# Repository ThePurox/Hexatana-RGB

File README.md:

# Hexatana
Hexatana is a 36 katana-inspired keyboard designed around [hexagonal keycaps](https://hw.s-ol.nu/HEX-keycaps/).

# Soldering
## MCU
The first step is to solder the RP2040 to the top center of the PCB.
You can use pin headers to align the MCU on the solder pads.
The orientation if the MCU should be such that the USB-C port is on the top side of the main PCB.
The bottom side of the main PCB has six katanas printed in its center.
So to solder the MCU in place, put the main PCB on your soldering surface, such that you do not see the six katanas, place the MCU onto of the PCB such that the USB-port is facing you.
You can now optionally stabilize the MCU with pin headers and solder the MCU to the main PCB.

## Soldering in the diodes
There exist two versions of the PCB, one has silkscreen marking for the orientation of the diodes, in the other one the shape of the solderpads indicates the direction of the diodes.

### silkscreen marking
On the top side of the PCB you will find a lot of `U`-shaped markings in with `Dx` where `x` is a number $\in \{1-36,73\}$ next to them
The top side of the diodes shows a vertical line followed by the letters T4, i.e. it looks like  `|T4`.
The diode has to be solder to the PCB such that the vertical line is on the closed side of the `U`-marking.
A soldered diode should look like the one in the following picture.

Solder in all 37 diodes that way.
Diodes `D1-D36` are in the center of the PCB, diode `D73` is $\approx 4\,\mathrm{cm}$ right of the MCU.

### Solderpad marking
To clean up the PCB the silkscreen markings for the diodes were removed.
The diodes shall be soldered in to the footprints were one pad is rectangular, and the other pad is pentagonal.
The pointy bit of the pentagon points to the kathode. I.e. the line marking on the diode need to be soldered to the rectangular pad.
The right direction is shown in the following picture.

Solder in all 37 diodes.
36 Diodes are in the center of the PCB, the final diode is $\approx 4\,\mathrm{cm}$ right of the MCU.

## Testing the keyboard
Now the keyboard should be functional.
You can test that by plugging the keyboard into a computer and opening a text editor of your choice.
Turn the keyboard around, such that you can see the 6 katanas and grab yourself a pair of metal tweezers or a pair of scissors.
Connect two adjacent solder pads.
A key press corresponding to the following keymap should be registered
<!-- Now a letter should appear on your keyboard. -->
<!-- Repeat these steps for all solderpads connected with white paint. -->
<!-- In your text editor you should see the letters `a-z` and the numbers `0-9`. -->
<!-- The default keymap of the keyboard is -->
```
  q w e r t      z u i o p
 a s d f g        h j k l OSS
y x c v b          n m , . -
    CTRL ESC    TAB ALT
        SPACE  ENTER
```
, where `OSS` is one-shot-shift.
Note the keymap presented here is show with the keyboard in its natural orientation.
You are probably holding it the other way round so you should a mirrored keymap.
If one of them didn't show up, this likely means that one of the diodes is not soldered in correctly.
When all keys work we can install the hot-swap sockets which will allow us to mount the switches.
However before we do those it is advisable to first install the optional LED-backlight.

## Backlight (optional)
### Soldering in the LEDs
It is now time to solder in the LEDs.
The PCB should be orientated such that you can see the 6 swords.
There are 36 small rectangular cutouts in the PCB (labeled `D37-D72`) in which the LEDs will be placed.
#### Orientation of the LEDs
The LEDs emit light only on one side (the one with the transparent cover).
This side needs to be placed face down, i.e. facing the table.
Now we still have one rotational degree of freedom, which we will eliminate in the following.
Just as the diodes, the light emitting diodes (LEDs) are sensitive to the orientation in which they are soldered in.
One of the metal legs of the LEDs is cut at an angle.
This leg has to be placed at the white `L`-shaped marking next to the hole for the LED.
This fixes the last rotational degree of freedom of each LED, and you can solder in the LEDs.
Be very careful with the orientation of the LEDs!
Their orientation changes when going from one row to the next row and going from the left side of the keyboard to the right side of the keyboard.
Only the thumb clusters are consistent in the orientation of the LEDs.
The LEDs are also very sensitive to temperature, so be careful when soldering them to the PCB.

### Picking a position for the solder jumper / picking a voltage for the first LED
Turn the keyboard around once more, such that you can no longer see the swords and the MCU is facing away from you.
#### Background
Approximately $3\,\mathrm{cm}$ to the right side of the MCU you will find a solder-jumper.
It is used to pick between two possible voltages powering the first LED of the backlight.
The datalines of the backlight-LEDs are not specified to work with the 3.3V supplied by the MCU, when the LEDs are driven by (the standard) 5V.
However usually they do still work in that scenario.
The PCB implements a hack [hack](https://hackaday.com/2017/01/20/cheating-at-5v-ws2812-control-to-use-a-3-3v-data-line/) for the unlucky chance that the LEDs do not work when the data line is driven by 3.3V and the LEDs are driven by 5V.
The hack exploits the fact, that when the first LED is powered by 4.3V, 3.3V are in spec for the dataline.
The solder jumper let's you pick whether the first LED is powered by 5V or 4.3V.
I suggest you try 5V first as all LEDs will have the same brightness that way.
Powering the first LED with a lower voltage might lead to a slightly dimmer first LED.

The center pad of the jumper is connected to the power line of the LED.
The bottom pad is connected to 5V.
The top pad has a voltage of 4.3V.
The diode just above the jumper reduces the 5V to 4.3V.

#### What to do
Bridge the center and bottom pads of the jumper, and connect the keyboard to a computer.
If all LEDs light up you can go ahead to soldering in the [hotswap sockets](#installing-the-hot-swap-sockets)
If some of the LEDs light up double check the solder joints of the LED with the highest number that is lighting up and the one with the smallest number that is not lighting up. There is most likely a problem there.
An Led might also be fried by excessive heat during soldering.
If the plastic of the LED has melted, the LED is probably dead; replace it with a new one. There a four more LEDs in the kit than you need.
If no LED lights up you might be one of the (un)lucky people with an LED produced to specification. There are two options on how to proceed.
1) you can try replacing the first LED (`D37`) and see whether the LEDs light up now, or
2) remove the solder from the solder jumper on the top side of the PCB and bridge the center pad with the top pad. Now the LED is powered with 4.3V and the 3.3V on the dataline are in spec.

### Installing stabilising capacitors (very optional)
There are 6 spots for capacitors next to the outer most switches of the top three key-rows.
The capacitors can be soldered onto the PCB to stabilise the power of the LEDs, however everything should work without them.

## Installing the hot-swap sockets
Turn the keyboard around, such that you can see the 6 swords again.
Now solder the hot-swap sockets onto the last solderpads that are not connected to anything yet.

## Installing the switches
Now turn the keyboard around one last time and install the switches and keycaps.

# Flashing Firmware
## QMK
The ncecessary files for a [QMK-firmware](https://qmk.fm) can be found in the [firmware directory](./qmk-firmware).
## VIAL
[Exen904](https://github.com/exen904) was so kind and build a [VIAL](https://get.vial.today/) firmware which can be found [here](https://github.com/exen904/vial-qmk/tree/exen904/keyboards/purox/hexatana)
## ZMK
There is a basic [zmk](https://github.com/ThePurox/hexatana-zmk/) repository.
Feel free to fork it and adjust everything to your liking.

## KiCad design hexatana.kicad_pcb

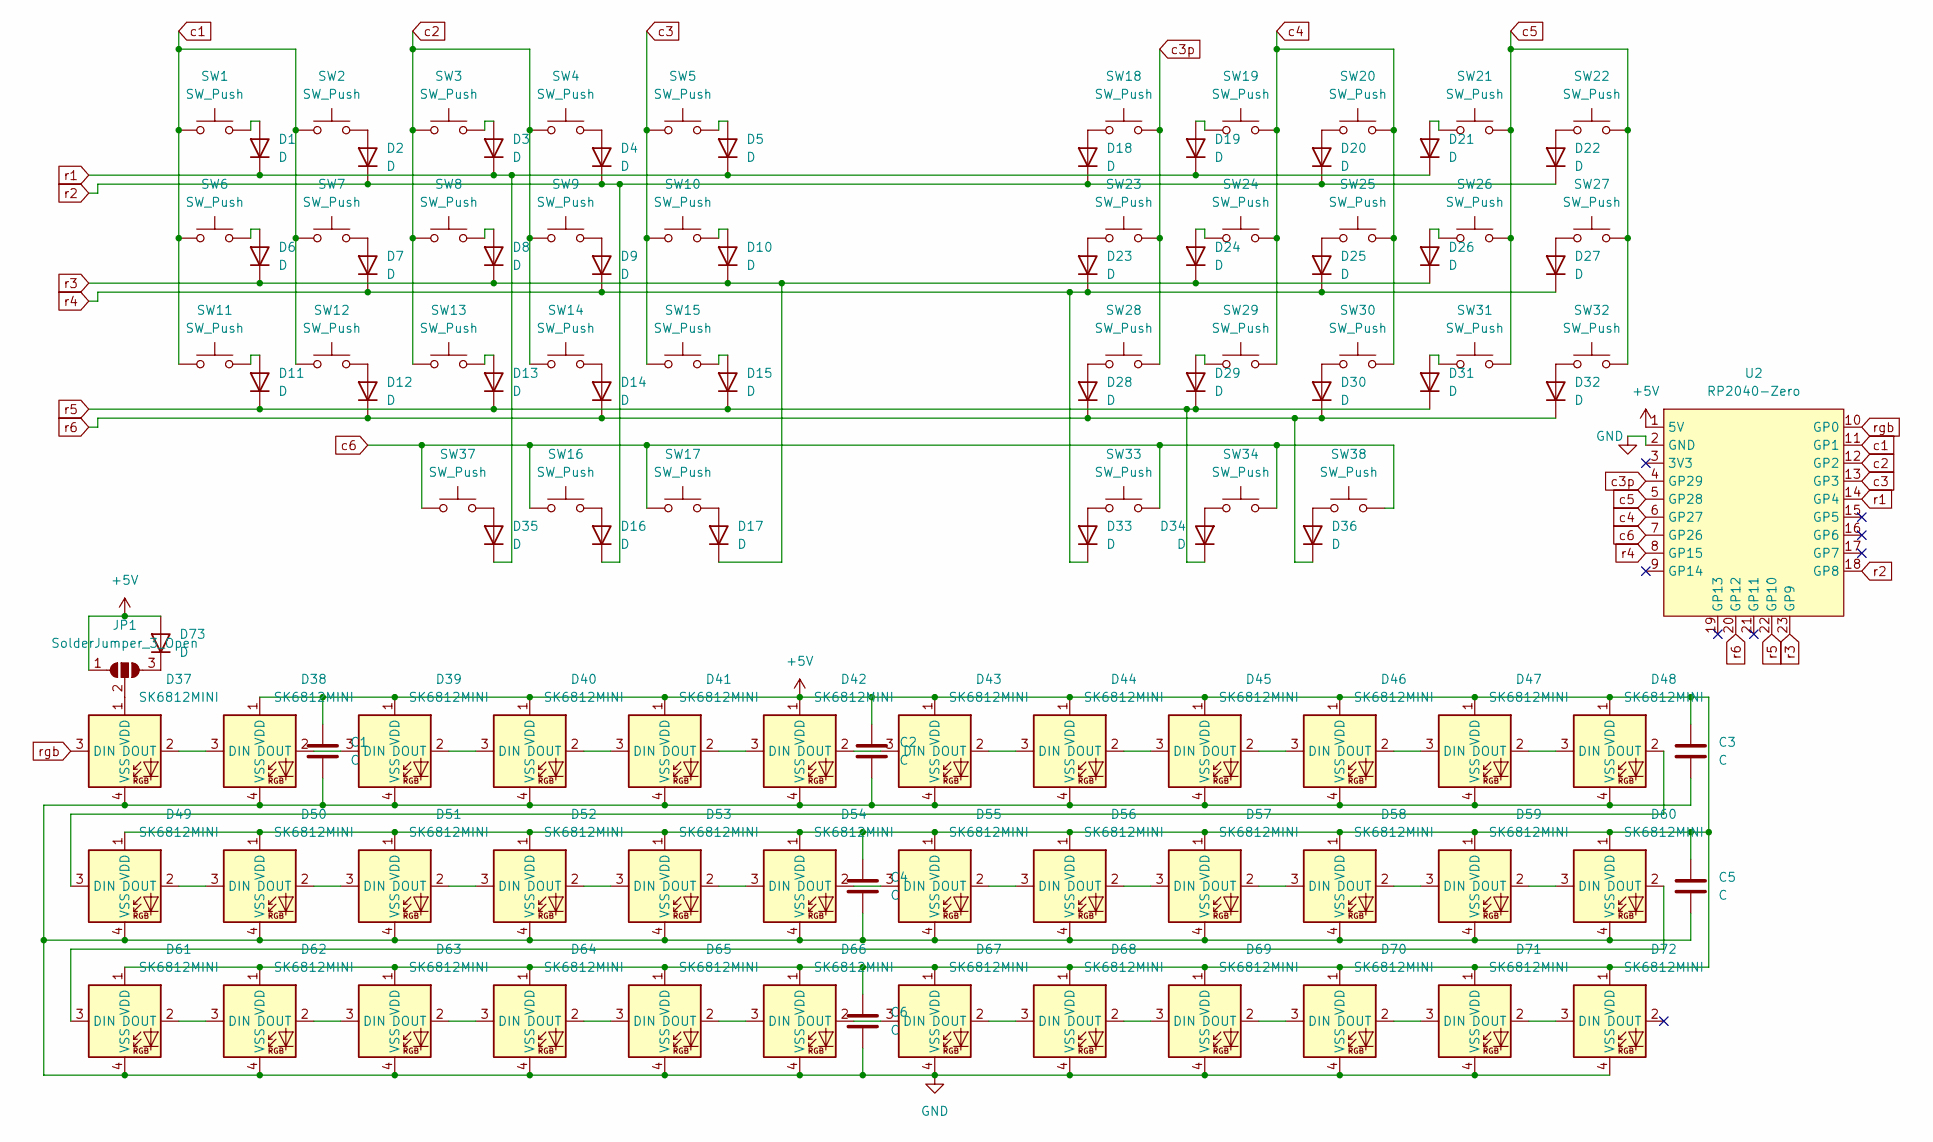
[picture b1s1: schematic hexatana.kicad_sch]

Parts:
C1, C2, C3, C4, C5, C6: C; C_0603_1608Metric_Pad1.08x0.95mm_HandSolder
D1, D2, D3, D4, D5, D6, D7, D8, D9, D10, D11, D12, D13, D14, D15, D16, D17, D18, D19, D20, D21, D22, D23, D24, D25, D26, D27, D28, D29, D30, D31, D32, D33, D34, D35, D36, D73: D; D_SOD-123
D37, D38, D39, D40, D41, D42, D43, D44, D45, D46, D47, D48, D49, D50, D51, D52, D53, D54, D55, D56, D57, D58, D59, D60, D61, D62, D63, D64, D65, D66, D67, D68, D69, D70, D71, D72: SK6812MINI; LED_6028R
JP1: SolderJumper_3_Open; SolderJumper-3_P1.3mm_Open_RoundedPad1.0x1.5mm
SW1, SW2, SW3, SW4, SW5, SW6, SW7, SW8, SW9, SW10, SW11, SW12, SW13, SW14, SW15, SW16, SW17, SW18, SW19, SW20, SW21, SW22, SW23, SW24, SW25, SW26, SW27, SW28, SW29, SW30, SW31, SW32, SW33, SW34, SW37, SW38: SW_Push; PG1350_hotswap
U2: RP2040-Zero; RP2040 Zero

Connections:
+5V: C1.1, C2.1, C3.1, C4.1, C5.1, C6.1, D38.1 (VDD), D39.1 (VDD), D40.1 (VDD), D41.1 (VDD), D42.1 (VDD), D43.1 (VDD), D44.1 (VDD), D45.1 (VDD), D46.1 (VDD), D47.1 (VDD), D48.1 (VDD), D49.1 (VDD), D50.1 (VDD), D51.1 (VDD), D52.1 (VDD), D53.1 (VDD), D54.1 (VDD), D55.1 (VDD), D56.1 (VDD), D57.1 (VDD), D58.1 (VDD), D59.1 (VDD), D60.1 (VDD), D61.1 (VDD), D62.1 (VDD), D63.1 (VDD), D64.1 (VDD), D65.1 (VDD), D66.1 (VDD), D67.1 (VDD), D68.1 (VDD), D69.1 (VDD), D70.1 (VDD), D71.1 (VDD), D72.1 (VDD), D73.2 (A), JP1.1 (A), U2.1 (5V)
GND: C1.2, C2.2, C3.2, C4.2, C5.2, C6.2, D37.4 (VSS), D38.4 (VSS), D39.4 (VSS), D40.4 (VSS), D41.4 (VSS), D42.4 (VSS), D43.4 (VSS), D44.4 (VSS), D45.4 (VSS), D46.4 (VSS), D47.4 (VSS), D48.4 (VSS), D49.4 (VSS), D50.4 (VSS), D51.4 (VSS), D52.4 (VSS), D53.4 (VSS), D54.4 (VSS), D55.4 (VSS), D56.4 (VSS), D57.4 (VSS), D58.4 (VSS), D59.4 (VSS), D60.4 (VSS), D61.4 (VSS), D62.4 (VSS), D63.4 (VSS), D64.4 (VSS), D65.4 (VSS), D66.4 (VSS), D67.4 (VSS), D68.4 (VSS), D69.4 (VSS), D70.4 (VSS), D71.4 (VSS), D72.4 (VSS), U2.2 (GND)
unnamed: D1.2 (A), SW1.2
unnamed: D2.2 (A), SW2.2
unnamed: D3.2 (A), SW3.2
unnamed: D4.2 (A), SW4.2
unnamed: D5.2 (A), SW5.2
unnamed: D6.2 (A), SW6.2
unnamed: D7.2 (A), SW7.2
unnamed: D8.2 (A), SW8.2
unnamed: D9.2 (A), SW9.2
unnamed: D10.2 (A), SW10.2
unnamed: D11.2 (A), SW11.2
unnamed: D12.2 (A), SW12.2
unnamed: D13.2 (A), SW13.2
unnamed: D14.2 (A), SW14.2
unnamed: D15.2 (A), SW15.2
unnamed: D16.2 (A), SW16.2
unnamed: D17.2 (A), SW17.2
unnamed: D18.2 (A), SW18.1
unnamed: D19.2 (A), SW19.1
unnamed: D20.2 (A), SW20.1
unnamed: D21.2 (A), SW21.1
unnamed: D22.2 (A), SW22.1
unnamed: D23.2 (A), SW23.1
unnamed: D24.2 (A), SW24.1
unnamed: D25.2 (A), SW25.1
unnamed: D26.2 (A), SW26.1
unnamed: D27.2 (A), SW27.1
unnamed: D28.2 (A), SW28.1
unnamed: D29.2 (A), SW29.1
unnamed: D30.2 (A), SW30.1
unnamed: D31.2 (A), SW31.1
unnamed: D32.2 (A), SW32.1
unnamed: D33.2 (A), SW33.1
unnamed: D34.2 (A), SW34.1
unnamed: D35.2 (A), SW37.2
unnamed: D36.2 (A), SW38.1
unnamed: D37.2 (DOUT), D38.3 (DIN)
unnamed: D37.1 (VDD), JP1.2 (C)
unnamed: D38.2 (DOUT), D39.3 (DIN)
unnamed: D39.2 (DOUT), D40.3 (DIN)
unnamed: D40.2 (DOUT), D41.3 (DIN)
unnamed: D41.2 (DOUT), D42.3 (DIN)
unnamed: D42.2 (DOUT), D43.3 (DIN)
unnamed: D43.2 (DOUT), D44.3 (DIN)
unnamed: D44.2 (DOUT), D45.3 (DIN)
unnamed: D45.2 (DOUT), D46.3 (DIN)
unnamed: D46.2 (DOUT), D47.3 (DIN)
unnamed: D47.2 (DOUT), D48.3 (DIN)
unnamed: D48.2 (DOUT), D49.3 (DIN)
unnamed: D49.2 (DOUT), D50.3 (DIN)
unnamed: D50.2 (DOUT), D51.3 (DIN)
unnamed: D51.2 (DOUT), D52.3 (DIN)
unnamed: D52.2 (DOUT), D53.3 (DIN)
unnamed: D53.2 (DOUT), D54.3 (DIN)
unnamed: D54.2 (DOUT), D55.3 (DIN)
unnamed: D55.2 (DOUT), D56.3 (DIN)
unnamed: D56.2 (DOUT), D57.3 (DIN)
unnamed: D57.2 (DOUT), D58.3 (DIN)
unnamed: D58.2 (DOUT), D59.3 (DIN)
unnamed: D59.2 (DOUT), D60.3 (DIN)
unnamed: D60.2 (DOUT), D61.3 (DIN)
unnamed: D61.2 (DOUT), D62.3 (DIN)
unnamed: D62.2 (DOUT), D63.3 (DIN)
unnamed: D63.2 (DOUT), D64.3 (DIN)
unnamed: D64.2 (DOUT), D65.3 (DIN)
unnamed: D65.2 (DOUT), D66.3 (DIN)
unnamed: D66.2 (DOUT), D67.3 (DIN)
unnamed: D67.2 (DOUT), D68.3 (DIN)
unnamed: D68.2 (DOUT), D69.3 (DIN)
unnamed: D69.2 (DOUT), D70.3 (DIN)
unnamed: D70.2 (DOUT), D71.3 (DIN)
unnamed: D71.2 (DOUT), D72.3 (DIN)
unnamed: D73.1 (K), JP1.3 (B)
c1: SW1.1, SW2.1, SW6.1, SW7.1, SW11.1, SW12.1, U2.11 (GP1)
c2: SW3.1, SW4.1, SW8.1, SW9.1, SW13.1, SW14.1, U2.12 (GP2)
c3: SW5.1, SW10.1, SW15.1, U2.13 (GP3)
c3p: SW18.2, SW23.2, SW28.2, U2.4 (GP29)
c4: SW19.2, SW20.2, SW24.2, SW25.2, SW29.2, SW30.2, U2.6 (GP27)
c5: SW21.2, SW22.2, SW26.2, SW27.2, SW31.2, SW32.2, U2.5 (GP28)
c6: SW16.1, SW17.1, SW33.2, SW34.2, SW37.1, SW38.2, U2.7 (GP26)
r1: D1.1 (K), D3.1 (K), D5.1 (K), D19.1 (K), D21.1 (K), D35.1 (K), U2.14 (GP4)
r2: D2.1 (K), D4.1 (K), D16.1 (K), D18.1 (K), D20.1 (K), D22.1 (K), U2.18 (GP8)
r3: D6.1 (K), D8.1 (K), D10.1 (K), D17.1 (K), D24.1 (K), D26.1 (K), U2.23 (GP9)
r4: D7.1 (K), D9.1 (K), D23.1 (K), D25.1 (K), D27.1 (K), D33.1 (K), U2.8 (GP15)
r5: D11.1 (K), D13.1 (K), D15.1 (K), D29.1 (K), D31.1 (K), D34.1 (K), U2.22 (GP10)
r6: D12.1 (K), D14.1 (K), D28.1 (K), D30.1 (K), D32.1 (K), D36.1 (K), U2.20 (GP12)
rgb: D37.3 (DIN), U2.10 (GP0)

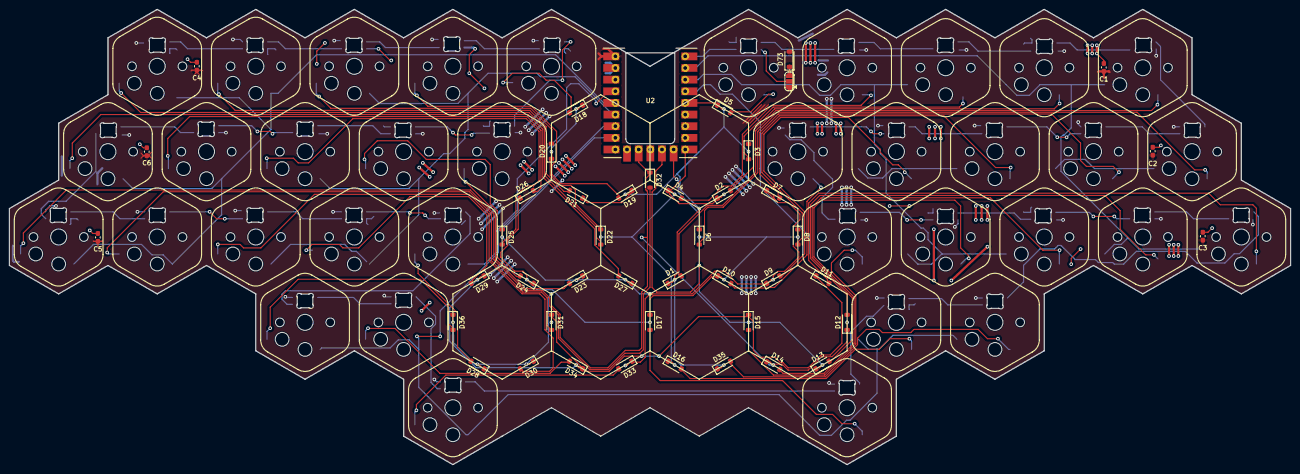
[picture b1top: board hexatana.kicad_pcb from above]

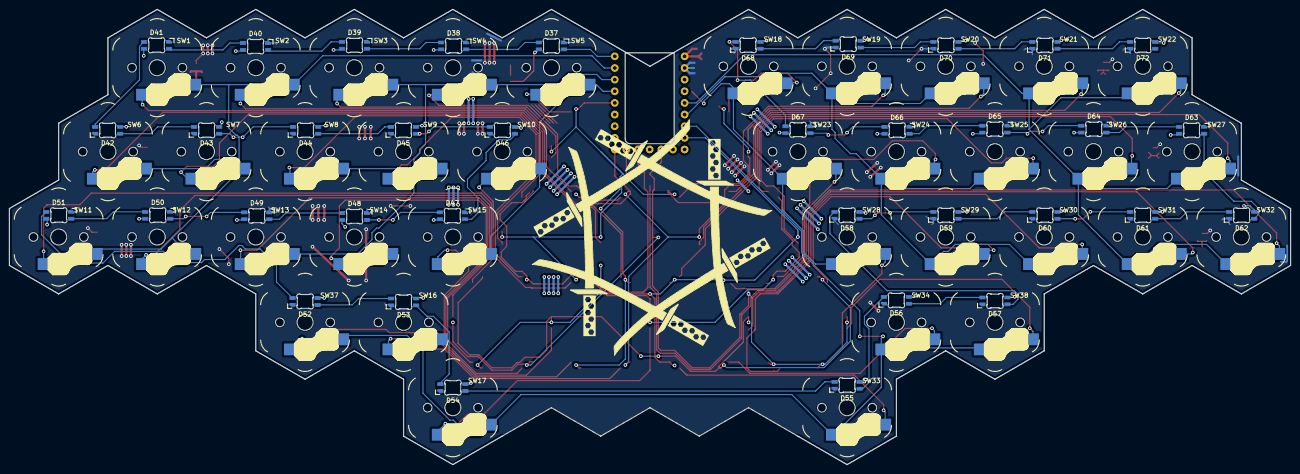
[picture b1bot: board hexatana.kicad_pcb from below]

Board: 2 copper layers, 279.5 x 99.3 mm, 117 parts (72 on the bottom side), 89 nets.

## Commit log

2024-01-08 simple version with ugly routing
2024-01-29 before hexed-ground
2024-02-17 final tm
2024-03-07 added Buildguide and qmk-firmware files
2024-03-07 added pictures
2024-03-07 proper pictures, fixed keymap
2024-03-07 fixed curly braces
2024-03-07 units
2024-03-07 fixed qmk link
2024-03-07 removed second readme
2024-03-07 added capacitors
2024-03-13 before rerouting
2024-03-16 rerouting done
2024-03-17 large diodes
2024-03-18 before ground-hexing
2024-03-18 done hexing
2024-03-19 removed diode front silk
2024-03-22 added picture of diodes and fixed qmk link
2024-07-01 added link to exens vial
2024-07-08 added description of other diode type
2024-07-08 fixed typo
2024-09-28 converted to gemini and added holes for case
2024-09-28 removed silkscreen for case holes
2024-09-29 added some extra hexes
2024-09-29 hexed ground much coarser
2024-11-27 added case
